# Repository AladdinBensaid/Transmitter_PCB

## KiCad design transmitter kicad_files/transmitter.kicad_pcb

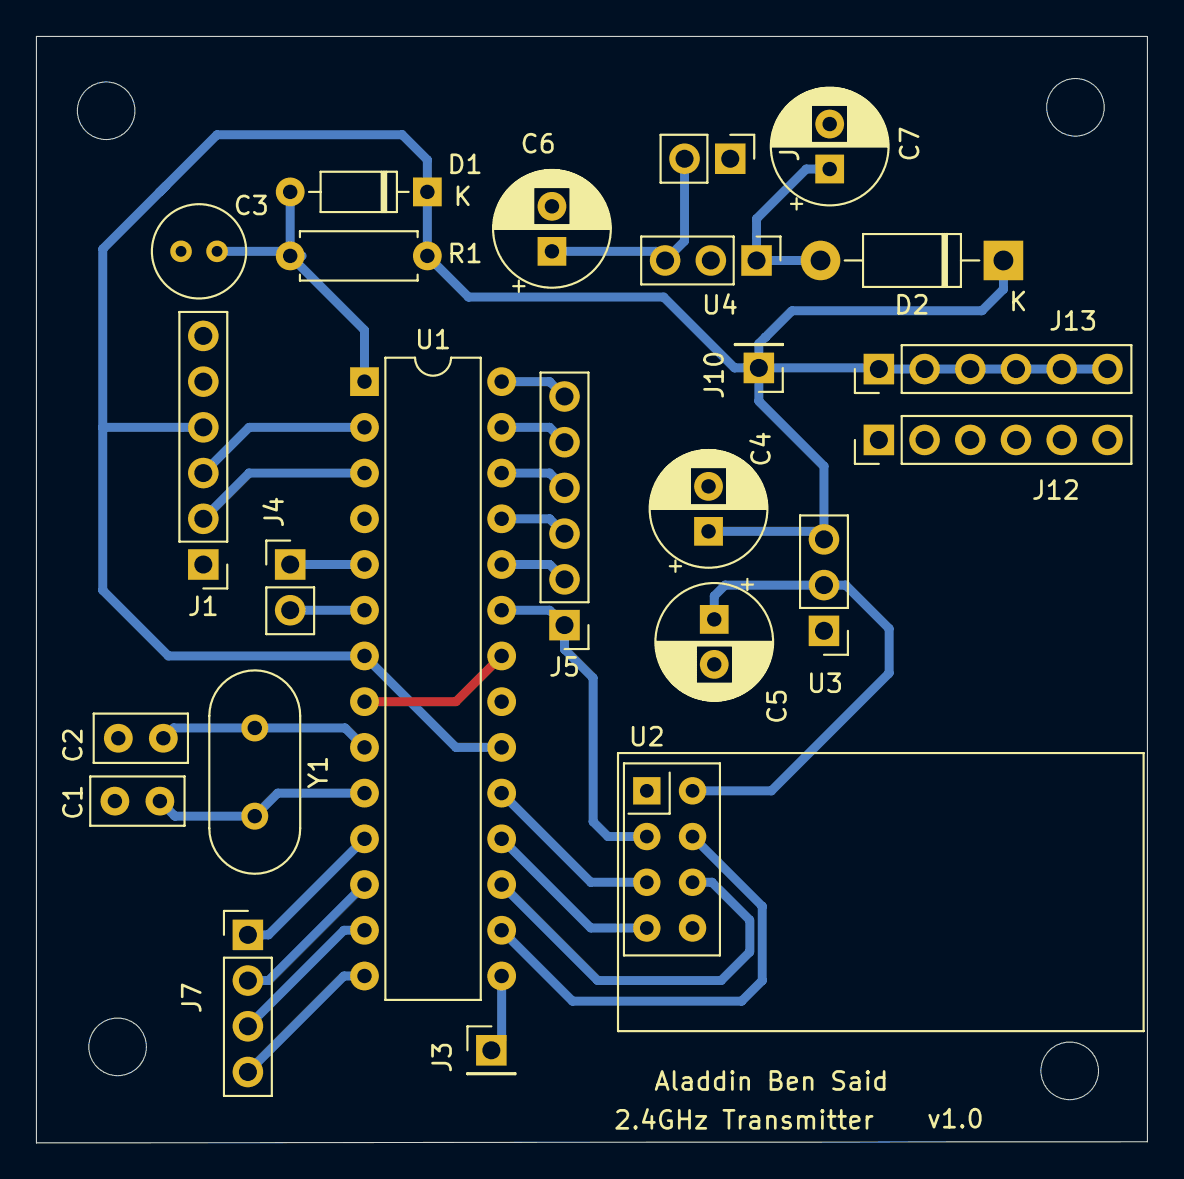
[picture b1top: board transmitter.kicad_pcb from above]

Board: 2 copper layers, 61.7 x 61.5 mm, 24 parts (0 on the bottom side), 27 nets.

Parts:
C1, C2: 22pF; C_Disc_D5.0mm_W2.5mm_P2.50mm
C3: C; C_Radial_D5.0mm_H7.0mm_P2.00mm
C4, C5, C6, C7: CP; CP_Radial_D6.3mm_P2.50mm
D1: 1N4148; D_DO-35_SOD27_P7.62mm_Horizontal
D2: 1N4001; D_DO-41_SOD81_P10.16mm_Horizontal
J1, J5, J12, J13: Screw_Terminal_01x06; PinHeader_1x06_P2.54mm_Vertical
J2, J4: Screw_Terminal_01x02; PinHeader_1x02_P2.54mm_Vertical
J3, J10: Screw_Terminal_01x01; PinHeader_1x01_P2.54mm_Vertical
J7: Screw_Terminal_01x04; PinHeader_1x04_P2.54mm_Vertical
R1: R; R_Axial_DIN0207_L6.3mm_D2.5mm_P7.62mm_Horizontal
U1: ATmega8L-8PU; DIP-28_W7.62mm
U2: NRF24L01_Breakout; nRF24L01_Breakout
U3: LD1117S33TR_SOT223; PinHeader_1x03_P2.54mm_Vertical
U4: LM78L05_TO92; PinHeader_1x03_P2.54mm_Vertical
Y1: 16Mhz; Crystal_HC18-U_Vertical

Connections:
+3V3: C5.1, U2.2, U3.2
+5V: C4.1, D1.1, D2.1, J1.4, J10.1, J13.1, J13.2, J13.3, J13.4, J13.5, J13.6, R1.2, U1.7, U1.20, U3.3
+12V: C6.1, J2.2, U4.3
CE: J5.1, U1.23, U2.3
CSN: U1.16, U2.4
GND: C1.2, C2.2, C4.2, C5.2, C6.2, C7.2, J1.6, J2.1, J12.1, J12.2, J12.3, J12.4, J12.5, J12.6, U1.8, U1.22, U2.1, U3.1, U4.2
MISO: U1.18, U2.7
MOSI: U1.17, U2.6
unnamed: C1.1, U1.10, Y1.2
unnamed: C2.1, U1.9, Y1.1
unnamed: C3.1, D1.2, R1.1, U1.1
unnamed: C7.1, D2.2, U4.1
unnamed: J3.1, U1.15
unnamed: J4.1, U1.5
unnamed: J4.2, U1.6
unnamed: J5.2, U1.24
unnamed: J5.3, U1.25
unnamed: J5.4, U1.26
unnamed: J5.5, U1.27
unnamed: J5.6, U1.28
unnamed: J7.1, U1.11
unnamed: J7.2, U1.12
unnamed: J7.3, U1.13
PB0: J7.4, U1.14
RX: J1.3, U1.2
SCK: U1.19, U2.5
TX: J1.2, U1.3

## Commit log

2023-02-08 first push
